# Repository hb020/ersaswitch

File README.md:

# ersaswitch

This project is about an external switch to an Ersa i-CON controller.
It allows switching between tools, without voiding Ersa warranty (at least, nothing from Ersa is opened and no wires are cut), and without occupying more desk space.

Inspired by https://www.eevblog.com/forum/reviews/ersa-i-con2v-(port-switch-hack)/

But I have an i-con 1V.

The switch has 3 states: left, right and a timed inbetween "no tool". The latter is mandatory between left/right tools for about 2 secs for the controller to not freak out. The switch is fully isolated, and via monitoring of the signals, switches itself on and off automatically in sync with the controller.

There is stuff inside this git repo about implementing communication with the tools to show "too hot to touch" temperatures of the disconnected tool, but that was put on hold, as I wanted to try out the Attiny 214. That guy would probably be too small for a full comms stack and it would require some more components and a lot more time.

Does the switch work well? Yes, and it is a joy too, since the heat up time of the tools is so short. Really easy to use. One big pushbutton. I designed it so that the relay click pattern gives audible hints too, so in short time you don't even have to look anymore as for what tool is active. You just grab it.

Is it economically viable? Probably not for a one-off, as the BOM gets close to 100 EUR if you have to buy it all (meaning: case and so) in small qty locally from Europe or the US. Just get the i-con 2V if you really use multiple tools regularly. But on the other hand you could use this to extend the port range of a 2V to 3 tools or more if you want (while keeping your warranty).

This should be easy to extend to 3 or more tools though. Just keep in mind that not all Ersa tools use only 5 wires. I have the i-tool and the Chip Tool Vario, and they only have 2 for power, 2 for logic, and 1 for earth. Some tools have more lines. If you have a tool with more lines, you'll have to change the relays.

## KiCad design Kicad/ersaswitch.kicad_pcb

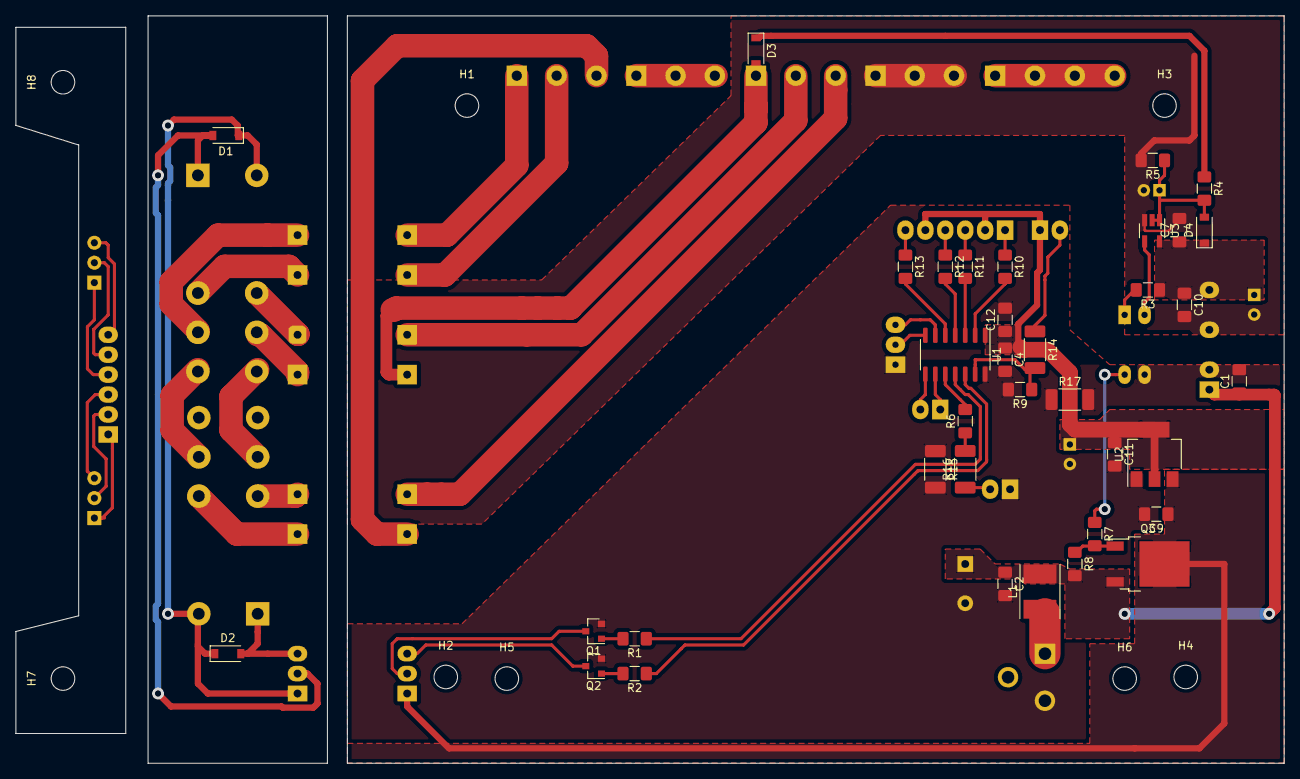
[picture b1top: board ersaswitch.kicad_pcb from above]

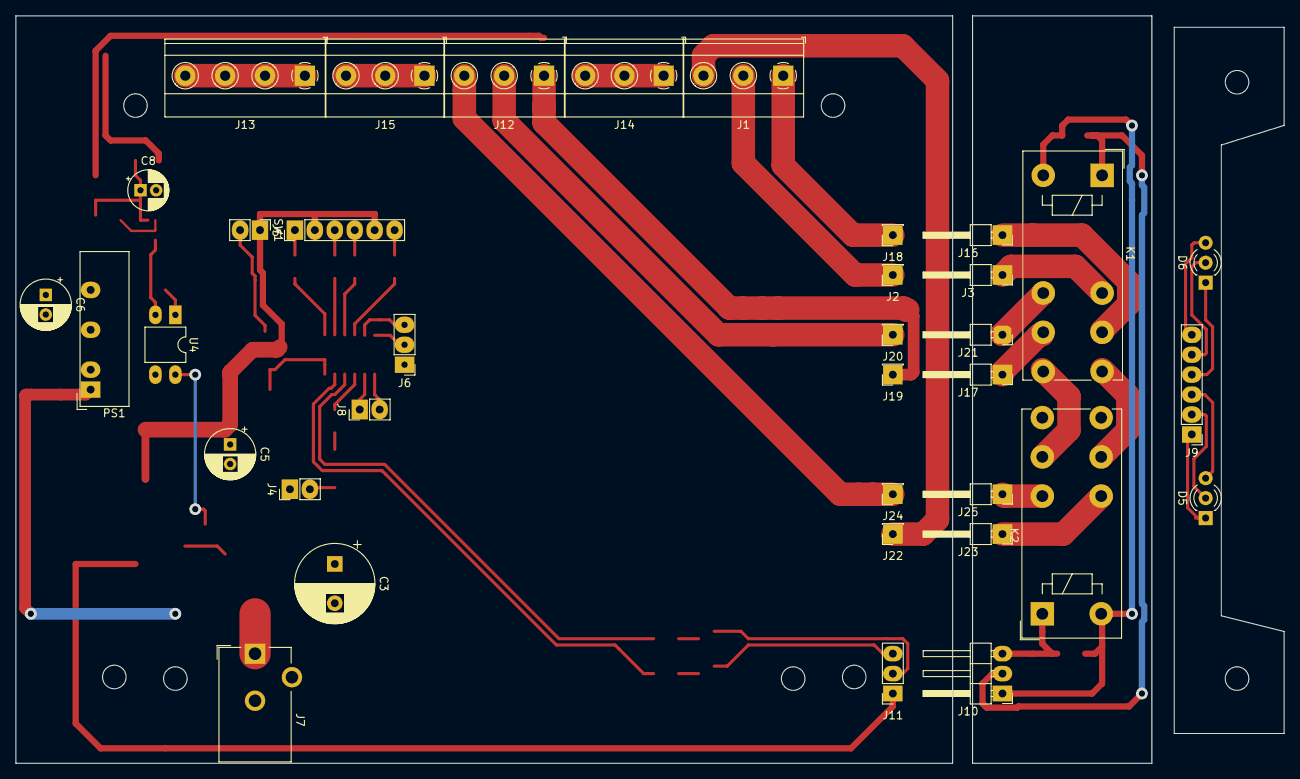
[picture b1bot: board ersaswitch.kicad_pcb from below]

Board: 2 copper layers, 161.6 x 95.2 mm, 80 parts (36 on the bottom side), 61 nets.

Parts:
C1, C2, C4, C7, C9, C10, C11, C12: 100nF; C_1206_3216Metric_Pad1.42x1.75mm_HandSolder
C3: 470uF; CP_Radial_D10.0mm_P5.00mm
C5, C6: 100uF; CP_Radial_D6.3mm_P2.50mm
C8: 4u7F; CP_Radial_D5.0mm_P2.00mm
D1, D2: 1N4001; D_SOD-123
D3, D4: 1N4148; D_SOD-123
D5: LED2_Dual_CAC; LED_D3.0mm-3
D6: LED1_Dual_CAC; LED_D3.0mm-3
H1, H2, H3, H4, H5, H6, H7, H8: MountingHole; MountingHole_3mm
J1, J12: Conn_01x03_Male; TerminalBlock_Phoenix_MKDS-1,5-3-5.08_1x03_P5.08mm_Horizont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
J2, J18, J19, J20, J22, J24: Conn_01x01_Female; PinSocket_1x01_P2.54mm_Vertical
J3, J16, J17, J21, J23, J25: Conn_01x01_Male; PinHeader_1x01_P2.54mm_Horizontal
J4, J8: Conn_01x02_Male; PinHeader_1x02_P2.54mm_Vertical_for_rivets
J5, J9: Conn_01x06_Male; PinHeader_1x06_P2.54mm_Vertical_for_rivets
J6: Conn_01x03_Male; PinHeader_1x03_P2.54mm_Vertical_biggerpads
J7: Barrel_Jack_Switch; BarrelJack_CUI_PJ-102AH_Horizontal
J10: Conn_01x03_Male; PinHeader_1x03_P2.54mm_Horizontal
J11: Conn_01x03_Female; PinSocket_1x03_P2.54mm_Vertical
J13: Conn_01x04_Male; TerminalBlock_Phoenix_MKDS-1,5-4-5.08_1x04_P5.08mm_Horizont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
J14, J15: Conn_01x03_Male; TerminalBlock_Phoenix_MKDS-1,5-3_1x03_P5.00mm_Horizontal
K1, K2: FINDER-41.52; Relay_DPDT_Finder_40.52
L1: 18uH; L_Taiyo-Yuden_NR-50xx_HandSoldering
PS1: B1205LS-1WR2; Converter_DCDC_BxxxxLS-1WR2
Q1, Q2: BC817; SOT-23
Q3: IRFR5305; TO-252-2
R1, R2, R6, R9: 4k7; R_1206_3216Metric_Pad1.42x1.75mm_HandSolder
R3: 1k?; R_1206_3216Metric_Pad1.42x1.75mm_HandSolder
R4, R8: 10k; R_1206_3216Metric_Pad1.42x1.75mm_HandSolder
R5: 1M; R_1206_3216Metric_Pad1.42x1.75mm_HandSolder
R7: 1k; R_1206_3216Metric_Pad1.42x1.75mm_HandSolder
R10, R12: 680; R_1206_3216Metric_Pad1.42x1.75mm_HandSolder
R11, R13: 470; R_1206_3216Metric_Pad1.42x1.75mm_HandSolder
R14, R15, R16, R17: 0R; R_2010_5025Metric_Pad1.52x2.65mm_HandSolder
SW1: SW_Push; PinHeader_1x02_P2.54mm_Vertical_for_rivets
U1: ATtiny214-SS; SOIC-14_3.9x8.7mm_P1.27mm
U2: AMS1117-5.0; SOT-223-3_TabPin2
U3: 74VHC1G132; SOT-23-5_HandSoldering
U4: PC817; DIP-4_W7.62mm_LongPads

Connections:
+5V: C4.1, C5.1, C11.1, C12.1, J5.2, J5.5, SW1.1, U1.1, U2.2
+5VA: C6.1, C7.1, C10.1, D4.1, PS1.6, R3.1, U3.5
+12C: C9.1, J11.1, Q3.2, U2.3
+12V: C1.1, C2.1, C3.1, L1.2, PS1.1, Q3.3, R8.2
/BTN: R9.1, R14.2, U1.13
/B_12V: D1.1, D2.1, J10.1, K1.A2, K2.A2
/B_HE+_1: J3.1, K1.12
/B_HE+_2: J23.1, K2.22
/B_HE+_IN: J16.1, K1.11
/B_PIO_1: J21.1, K1.22
/B_PIO_2: J25.1, K2.12
/B_PIO_IN: J17.1, K1.21
/B_Rel1: D1.2, J10.2, K1.A1
/B_Rel2: D2.2, J10.3, K2.A1
/HE+_1: J1.2, J2.1
/HE+_2: J1.3, J22.1
/HE+_IN: J1.1, J18.1
/LED1_G: J5.6, R13.1
/LED1_R: J5.4, R12.1
/LED2_G: J5.3, R11.1
/LED2_R: J5.1, R10.1
/PIO_1: J12.2, J20.1
/PIO_2: J12.3, J24.1
/PIO_IN: D3.2, J12.1, J19.1
/Rel1: R1.1, U1.11
/Rel2: R2.1, U1.12
/RxD: J6.3, U1.6
/T_Rel1: J11.2, Q1.3
/T_Rel2: J11.3, Q2.3
/TxD: J6.2, U1.7
GND: C1.2, C2.2, C3.2, C4.2, C5.2, C9.2, C11.2, C12.2, J4.1, J6.1, J7.2, PS1.2, Q1.2, Q2.2, R9.2, R15.1, R15.2, R17.1, R17.2, U1.14, U2.1, U4.3
GNDA: C6.2, C7.2, C8.2, C10.2, J15.1, J15.2, J15.3, PS1.4, R5.2, U3.3
unnamed: C8.1, D4.2, R4.2, R5.1, U3.1, U3.2
unnamed: D3.1, R4.1
unnamed: D5.1, J9.1
unnamed: D5.2, J9.2
unnamed: D5.3, J9.3
unnamed: D6.1, J9.4
unnamed: D6.2, J9.5
unnamed: D6.3, J9.6
unnamed: J4.2, R16.1
unnamed: J7.1, L1.1
unnamed: J8.1, U1.9
unnamed: J8.2, U1.8
unnamed: J13.1, J13.2, J13.3, J13.4
unnamed: J14.1, J14.2, J14.3
unnamed: K1.14, K2.21
unnamed: K1.24, K2.11
unnamed: Q1.1, R1.2
unnamed: Q2.1, R2.2
unnamed: Q3.1, R7.2, R8.1
unnamed: R3.2, U4.1
unnamed: R6.2, U1.10
unnamed: R7.1, U4.4
unnamed: R10.2, U1.2
unnamed: R11.2, U1.3
unnamed: R12.2, U1.4
unnamed: R13.2, U1.5
unnamed: R14.1, SW1.2
unnamed: R6.1, R16.2
unnamed: U3.4, U4.2

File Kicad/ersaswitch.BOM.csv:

Ref;Value;Footprint
C1;100nF;Capacitor_SMD:C_1206_3216Metric_Pad1.42x1.75mm_HandSolder
C2;100nF;Capacitor_SMD:C_1206_3216Metric_Pad1.42x1.75mm_HandSolder
C3;470uF;Capacitor_THT:CP_Radial_D10.0mm_P5.00mm
C4;100nF;Capacitor_SMD:C_1206_3216Metric_Pad1.42x1.75mm_HandSolder
C5;100uF;Capacitor_THT:CP_Radial_D6.3mm_P2.50mm
C6;100uF;Capacitor_THT:CP_Radial_D6.3mm_P2.50mm
C7;100nF;Capacitor_SMD:C_1206_3216Metric_Pad1.42x1.75mm_HandSolder
C8;4u7F;Capacitor_THT:CP_Radial_D5.0mm_P2.00mm
C9;100nF;Capacitor_SMD:C_1206_3216Metric_Pad1.42x1.75mm_HandSolder
C10;100nF;Capacitor_SMD:C_1206_3216Metric_Pad1.42x1.75mm_HandSolder
C11;100nF;Capacitor_SMD:C_1206_3216Metric_Pad1.42x1.75mm_HandSolder
C12;100nF;Capacitor_SMD:C_1206_3216Metric_Pad1.42x1.75mm_HandSolder
D1;1N4001;Diode_SMD:D_SOD-123
D2;1N4001;Diode_SMD:D_SOD-123
D3;1N4148;Diode_SMD:D_SOD-123
D4;1N4148;Diode_SMD:D_SOD-123
D5;LED2_Dual_CAC;LED_THT:LED_D3.0mm-3
D6;LED1_Dual_CAC;LED_THT:LED_D3.0mm-3
H1;MountingHole;MountingHole:MountingHole_3mm
H2;MountingHole;MountingHole:MountingHole_3mm
H3;MountingHole;MountingHole:MountingHole_3mm
H4;MountingHole;MountingHole:MountingHole_3mm
H5;MountingHole;MountingHole:MountingHole_3mm
H6;MountingHole;MountingHole:MountingHole_3mm
H7;MountingHole;MountingHole:MountingHole_3mm
H8;MountingHole;MountingHole:MountingHole_3mm
J1;Conn_01x03_Male;TerminalBlock_Phoenix:TerminalBlock_Phoenix_MKDS-1,5-3-5.08_1x03_P5.08mm_Horizontal
J2;Conn_01x01_Female;Connector_PinSocket_2.54mm:PinSocket_1x01_P2.54mm_Vertical
J3;Conn_01x01_Male;Connector_PinHeader_2.54mm:PinHeader_1x01_P2.54mm_Horizontal
J4;Conn_01x02_Male;mylib:PinHeader_1x02_P2.54mm_Vertical_for_rivets
J5;Conn_01x06_Male;mylib:PinHeader_1x06_P2.54mm_Vertical_for_rivets
J6;Conn_01x03_Male;mylib:PinHeader_1x03_P2.54mm_Vertical_biggerpads
J7;Barrel_Jack_Switch;Connector_BarrelJack:BarrelJack_CUI_PJ-102AH_Horizontal
J8;Conn_01x02_Male;mylib:PinHeader_1x02_P2.54mm_Vertical_for_rivets
J9;Conn_01x06_Male;mylib:PinHeader_1x06_P2.54mm_Vertical_for_rivets
J10;Conn_01x03_Male;Connector_PinHeader_2.54mm:PinHeader_1x03_P2.54mm_Horizontal
J11;Conn_01x03_Female;Connector_PinSocket_2.54mm:PinSocket_1x03_P2.54mm_Vertical
J12;Conn_01x03_Male;TerminalBlock_Phoenix:TerminalBlock_Phoenix_MKDS-1,5-3-5.08_1x03_P5.08mm_Horizontal
J13;Conn_01x04_Male;TerminalBlock_Phoenix:TerminalBlock_Phoenix_MKDS-1,5-4-5.08_1x04_P5.08mm_Horizontal
J14;Conn_01x03_Male;TerminalBlock_Phoenix:TerminalBlock_Phoenix_MKDS-1,5-3_1x03_P5.00mm_Horizontal
J15;Conn_01x03_Male;TerminalBlock_Phoenix:TerminalBlock_Phoenix_MKDS-1,5-3_1x03_P5.00mm_Horizontal
J16;Conn_01x01_Male;Connector_PinHeader_2.54mm:PinHeader_1x01_P2.54mm_Horizontal
J17;Conn_01x01_Male;Connector_PinHeader_2.54mm:PinHeader_1x01_P2.54mm_Horizontal
J18;Conn_01x01_Female;Connector_PinSocket_2.54mm:PinSocket_1x01_P2.54mm_Vertical
J19;Conn_01x01_Female;Connector_PinSocket_2.54mm:PinSocket_1x01_P2.54mm_Vertical
J20;Conn_01x01_Female;Connector_PinSocket_2.54mm:PinSocket_1x01_P2.54mm_Vertical
J21;Conn_01x01_Male;Connector_PinHeader_2.54mm:PinHeader_1x01_P2.54mm_Horizontal
J22;Conn_01x01_Female;Connector_PinSocket_2.54mm:PinSocket_1x01_P2.54mm_Vertical
J23;Conn_01x01_Male;Connector_PinHeader_2.54mm:PinHeader_1x01_P2.54mm_Horizontal
J24;Conn_01x01_Female;Connector_PinSocket_2.54mm:PinSocket_1x01_P2.54mm_Vertical
J25;Conn_01x01_Male;Connector_PinHeader_2.54mm:PinHeader_1x01_P2.54mm_Horizontal
K1;FINDER-41.52;Relay_THT:Relay_DPDT_Finder_40.52
K2;FINDER-41.52;Relay_THT:Relay_DPDT_Finder_40.52
L1;18uH;Inductor_SMD:L_Taiyo-Yuden_NR-50xx_HandSoldering
PS1;B1205LS-1WR2;mylib:Converter_DCDC_BxxxxLS-1WR2
Q1;BC817;Package_TO_SOT_SMD:SOT-23
Q2;BC817;Package_TO_SOT_SMD:SOT-23
Q3;IRFR5305;Package_TO_SOT_SMD:TO-252-2
R1;4k7;Resistor_SMD:R_1206_3216Metric_Pad1.42x1.75mm_HandSolder
R2;4k7;Resistor_SMD:R_1206_3216Metric_Pad1.42x1.75mm_HandSolder
R3;1k?;Resistor_SMD:R_1206_3216Metric_Pad1.42x1.75mm_HandSolder
R4;10k;Resistor_SMD:R_1206_3216Metric_Pad1.42x1.75mm_HandSolder
R5;1M;Resistor_SMD:R_1206_3216Metric_Pad1.42x1.75mm_HandSolder
R6;4k7;Resistor_SMD:R_1206_3216Metric_Pad1.42x1.75mm_HandSolder
R7;1k;Resistor_SMD:R_1206_3216Metric_Pad1.42x1.75mm_HandSolder
R8;10k;Resistor_SMD:R_1206_3216Metric_Pad1.42x1.75mm_HandSolder
R9;4k7;Resistor_SMD:R_1206_3216Metric_Pad1.42x1.75mm_HandSolder
R10;680;Resistor_SMD:R_1206_3216Metric_Pad1.42x1.75mm_HandSolder
R11;470;Resistor_SMD:R_1206_3216Metric_Pad1.42x1.75mm_HandSolder
R12;680;Resistor_SMD:R_1206_3216Metric_Pad1.42x1.75mm_HandSolder
R13;470;Resistor_SMD:R_1206_3216Metric_Pad1.42x1.75mm_HandSolder
R14;0R;Resistor_SMD:R_2010_5025Metric_Pad1.52x2.65mm_HandSolder
R15;0R;Resistor_SMD:R_2010_5025Metric_Pad1.52x2.65mm_HandSolder
R16;0R;Resistor_SMD:R_2010_5025Metric_Pad1.52x2.65mm_HandSolder
R17;0R;Resistor_SMD:R_2010_5025Metric_Pad1.52x2.65mm_HandSolder
SW1;SW_Push (connection);mylib:PinHeader_1x02_P2.54mm_Vertical_for_rivets
U1;ATtiny214-SS;Package_SO:SOIC-14_3.9x8.7mm_P1.27mm
U2;AMS1117-5.0;Package_TO_SOT_SMD:SOT-223-3_TabPin2
U3;74VHC1G132;Package_TO_SOT_SMD:SOT-23-5_HandSoldering
U4;PC817;Package_DIP:DIP-4_W7.62mm_LongPads
;;
;;
Ref;Value;qty
Case;Hammond 1598BBBK;1
DIN plug;PREHKEYTEC 71430-080/0800;1
DIN socket;"PREHKEYTEC 	71206-080/0800";2
Support for relay;"Finder 	95.15.2SMA";2
PCB feet;TR FASTENINGS TRLCBSBM-4-01A2-RT -  PCB Support, Lock-In Support With Adhesive Base, Nylon 6.6, 6.4mm x 4.4mm;2
PCB feet;TR FASTENINGS TRLCBSBM-3-01A2-RT -  PCB Support, Lock-In Support With Adhesive Base, Nylon 6.6, 4.8mm x 4.4mm;2
Pushbutton;Multicomp MCPS23B-2 -  Pushbutton Switch, Standard, 12 mm, SPST, (On)-Off, Square Raised;1
fasteners;;various
cabling;;various

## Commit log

2020-05-08 First commit to public Git
2020-05-09 Update README.md
    silly grammar edit
2023-04-13 better with PDFs
